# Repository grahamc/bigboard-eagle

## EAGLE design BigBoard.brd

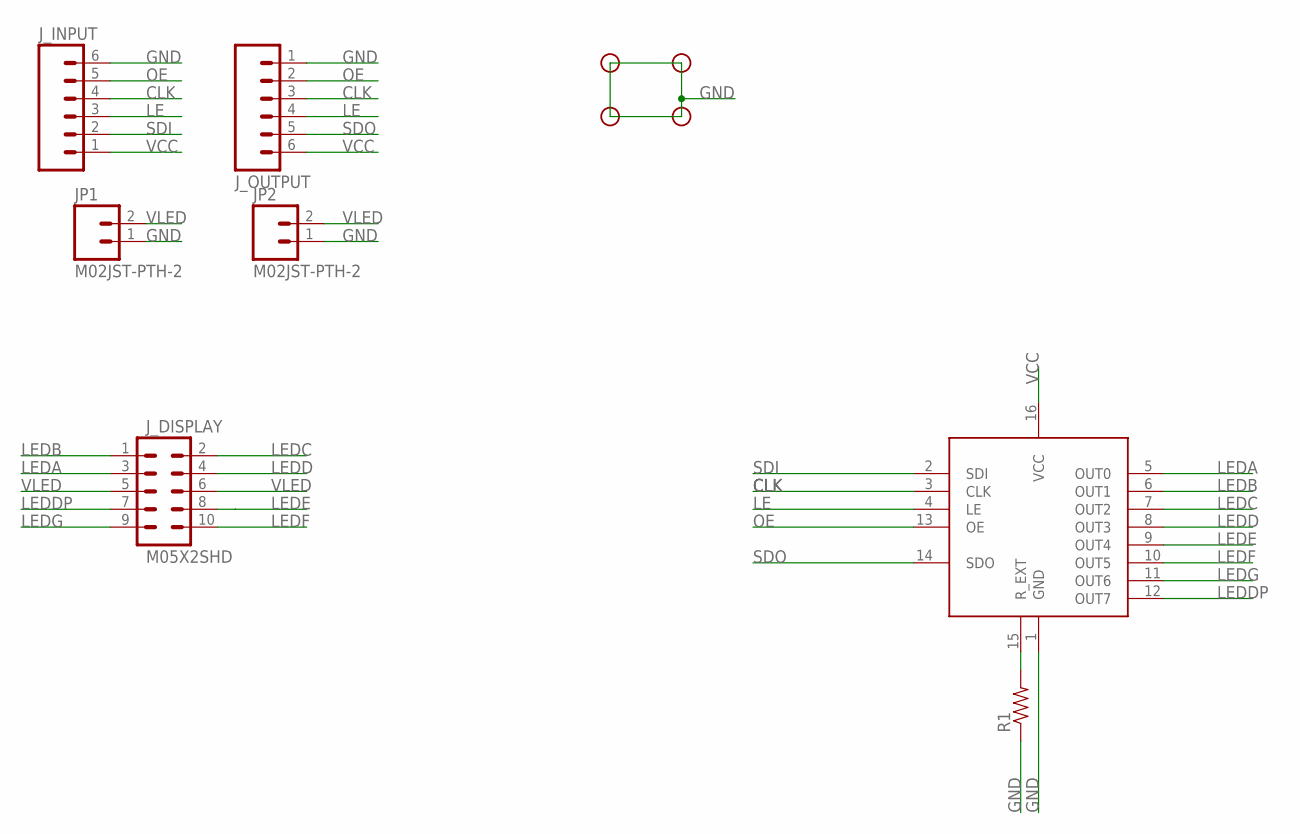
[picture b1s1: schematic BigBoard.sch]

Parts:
JP1, JP2: M02JST-PTH-2; JST-2-PTH
J_DISPLAY: M05X2SHD; 2X5-SHROUDED
J_INPUT: M06POLAR; MOLEX-1X6
J_OUTPUT: M06POLAR; MOLEX-1X6
R1: RESISTOR0603-RES; 0603-RES
STANDOFF1, STANDOFF2, STANDOFF3, STANDOFF4: STAND-OFF
U$2: A6278EA

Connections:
CLK: J_INPUT.4, J_OUTPUT.3, U$2.3 (CLK)
GND: JP1.1, JP2.1, J_INPUT.6, J_OUTPUT.1, R1.1, U$2.1 (GND)
LE: J_INPUT.3, J_OUTPUT.4, U$2.4 (LE)
LEDA: J_DISPLAY.3, U$2.5 (OUT0)
LEDB: J_DISPLAY.1, U$2.6 (OUT1)
LEDC: J_DISPLAY.2, U$2.7 (OUT2)
LEDD: J_DISPLAY.4, U$2.8 (OUT3)
LEDDP: J_DISPLAY.7, U$2.12 (OUT7)
LEDE: J_DISPLAY.8, U$2.9 (OUT4)
LEDF: J_DISPLAY.10, U$2.10 (OUT5)
LEDG: J_DISPLAY.9, U$2.11 (OUT6)
unnamed: R1.2, U$2.15 (R_EXT)
OE: J_INPUT.5, J_OUTPUT.2, U$2.13 (OE)
SDI: J_INPUT.2, U$2.2 (SDI)
SDO: J_OUTPUT.5, U$2.14 (SDO)
VCC: J_INPUT.1, J_OUTPUT.6, U$2.16 (VCC)
VLED: JP1.2, JP2.2, J_DISPLAY.5, J_DISPLAY.6

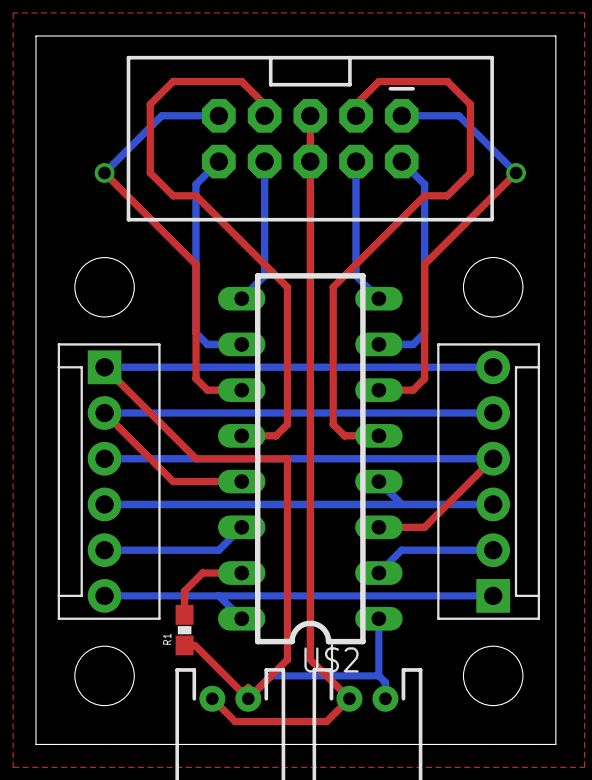
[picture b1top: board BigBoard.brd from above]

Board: 2 copper layers, 28.9 x 39.4 mm, 11 parts (0 on the bottom side), 17 nets.

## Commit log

2014-04-10 I don't even
2014-04-22 don't need thos efiles
2014-04-22 Replace 0805 resistor with 0603

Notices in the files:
parts and their libraries:
SparkFun-Connectors: Licensing: Creative Commons ShareAlike 4.0 International - https://creativecommons.org/licenses/by-sa/4.0
